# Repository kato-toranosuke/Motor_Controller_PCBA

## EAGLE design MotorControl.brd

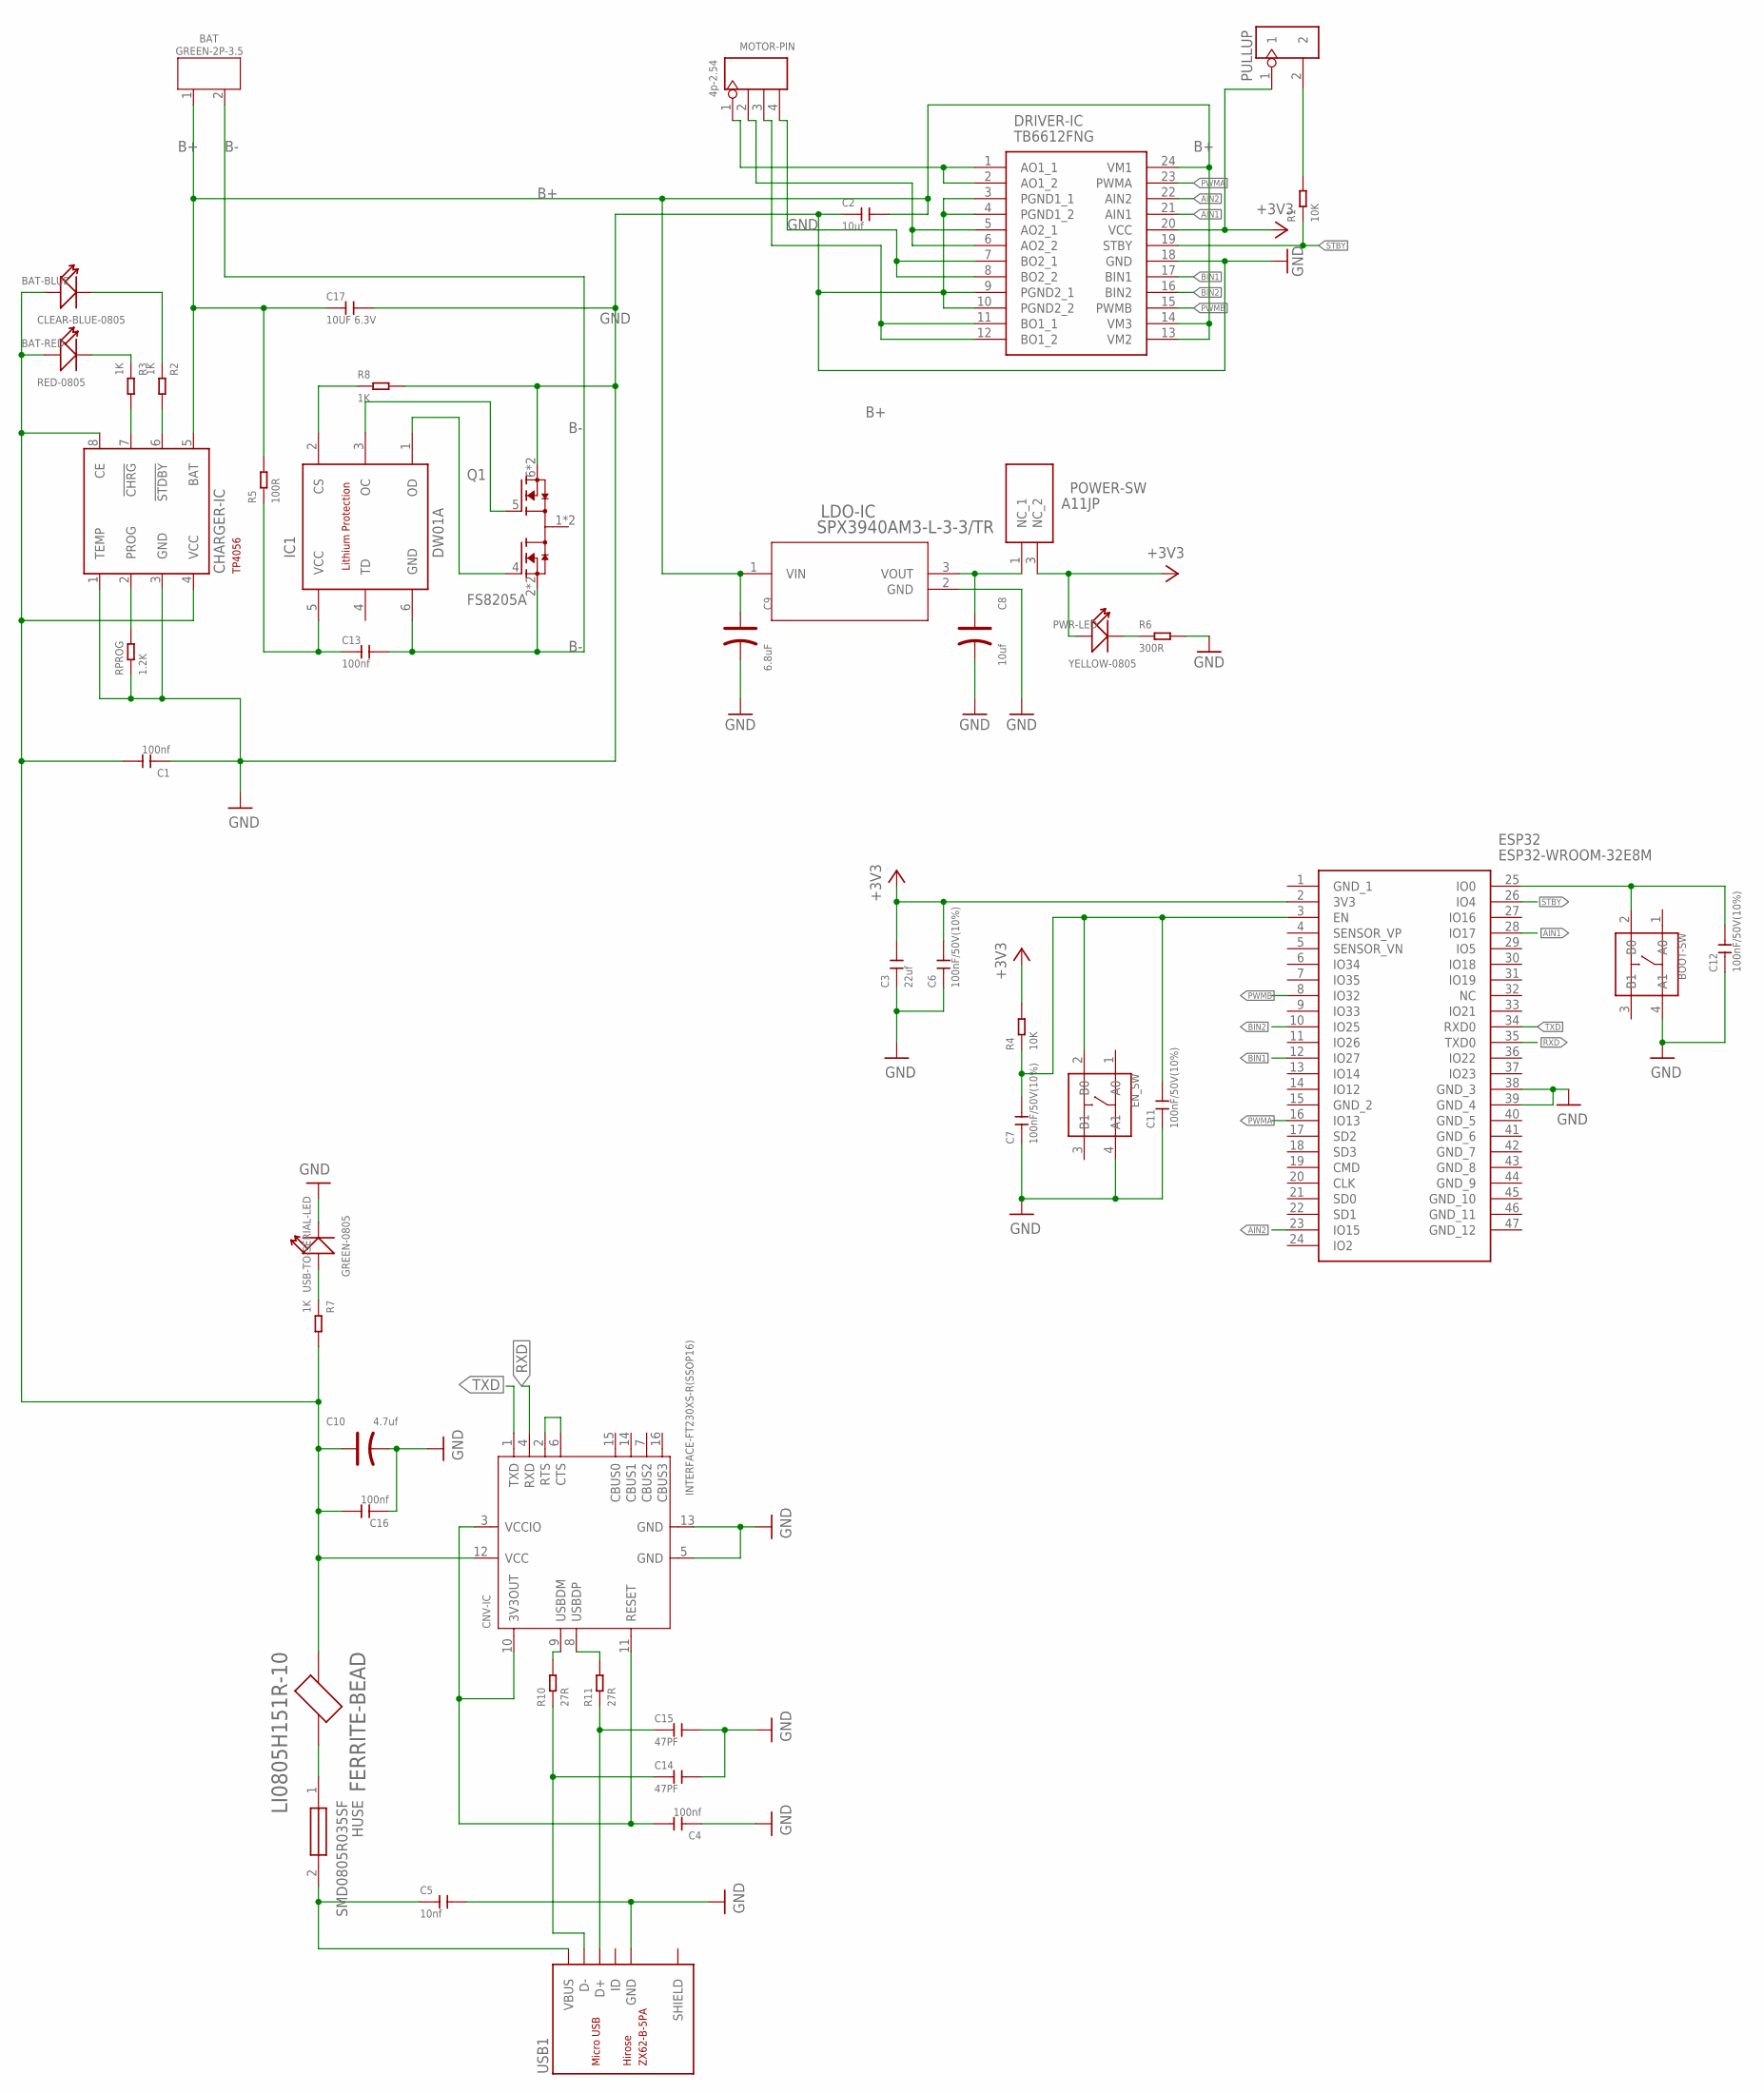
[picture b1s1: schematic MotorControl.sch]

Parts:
BAT: GREEN-2P-3.5; H2-3.5-7.0X7.0MM
BAT-BLUE: CLEAR-BLUE-0805; LED-0805
BAT-RED: RED-0805; LED-0805
BOOT-SW: SMD-SWITCH-TACTILE-SPST-NO(4P-D6.0MM); SW4-SMD-6.0X6.0X5.0MM
C1, C4, C13, C16: 100nf; C0805
C2: 10uf; C1206
C3: 22uf; C0805
C5: 10nf; C0805
C6, C7, C11, C12: 100nF/50V(10%); C0603
C8: 10uf; AVX-A
C9: 6.8uF; CAPPM3528X210N
C10: 4.7uf; AVX-A
C14, C15: 47PF; C0402
C17: 10UF 6.3V; C0603
CHARGER-IC: TP4056; SOT23-8; MPN TP4056
CNV-IC: INTERFACE-FT230XS-R(SSOP16); SSOP16-0.635-5X4MM
DRIVER-IC: TB6612FNG; SOP65P760X160-24N
EN_SW: SMD-SWITCH-TACTILE-SPST-NO(4P-D6.0MM); SW4-SMD-6.0X6.0X5.0MM
ESP32: ESP32-WROOM-32E8M; ESP32WROOM32E8MB
FERRITE-BEAD: LI0805H151R-10; FB_LI0805H151R-10
HUSE: SMD0805R035SF; MPN SMD0805R035SF
IC1: DW01A; SOT23-6
LDO-IC: SPX3940AM3-L-3-3/TR; SOT-223-3_VAR-AA
MOTOR-PIN: 4p-2.54; H4-2.54
POWER-SW: A11JP
PULLUP: DIP-BLACK-JUMPER; H2-2.54
PWR-LED: YELLOW-0805; LED-0805
Q1: FS8205A; SOP65P640X120-8N
R1, R4: 10K; R0603
R2, R3, R7: 1K; R0603
R5: 100R; R1206
R6: 300R; R0603
R8: 1K; R0805
R10, R11: 27R; R0805
RPROG: 1.2K; R0805
USB1: ZX62-B-5PA; MICRO-USB5+6P-SMD-0.65-AB
USB-TO-SERIAL-LED: GREEN-0805; LED-0805

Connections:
+3V3: C3.2, C6.2, DRIVER-IC.20 (VCC), ESP32.2 (3V3), POWER-SW.3 (NC_2), PULLUP.1, PWR-LED.+, R4.2
AIN1: DRIVER-IC.21 (AIN1), ESP32.28 (IO17)
AIN2: DRIVER-IC.22 (AIN2), ESP32.23 (IO15)
AO1: DRIVER-IC.1 (AO1_1), DRIVER-IC.2 (AO1_2), MOTOR-PIN.1
AO2: DRIVER-IC.5 (AO2_1), DRIVER-IC.6 (AO2_2), MOTOR-PIN.2
B+: BAT.1, C2.2, C9.1 (+), C17.1, CHARGER-IC.5 (BAT), DRIVER-IC.13 (VM2), DRIVER-IC.14 (VM3), DRIVER-IC.24 (VM1), LDO-IC.1 (VIN), R5.2
B-: BAT.2, C13.2, IC1.6 (GND), Q1.2 (S1), Q1.3 (S1)
BIN1: DRIVER-IC.17 (BIN1), ESP32.12 (IO27)
BIN2: DRIVER-IC.16 (BIN2), ESP32.10 (IO25)
BO1: DRIVER-IC.11 (BO1_1), DRIVER-IC.12 (BO1_2), MOTOR-PIN.3
BO2: DRIVER-IC.7 (BO2_1), DRIVER-IC.8 (BO2_2), MOTOR-PIN.4
GND: BOOT-SW.4 (A1), C1.1, C2.1, C3.1, C4.1, C5.2, C6.1, C7.1, C8.-, C9.2 (-), C10.-, C11.1, C12.1, C14.2, C15.2, C16.1, C17.2, CHARGER-IC.1 (TEMP), CHARGER-IC.3 (GND), CNV-IC.5 (GND), CNV-IC.13 (GND), DRIVER-IC.3 (PGND1_1), DRIVER-IC.4 (PGND1_2), DRIVER-IC.9 (PGND2_1), DRIVER-IC.10 (PGND2_2), DRIVER-IC.18 (GND), EN_SW.4 (A1), ESP32.38 (GND_3), ESP32.39 (GND_4), LDO-IC.2 (GND), Q1.6 (S2), Q1.7 (S2), R6.2, R8.2, RPROG.1, USB1.5 (GND), USB-TO-SERIAL-LED.-
unnamed: IC1.3 (OC), Q1.5 (G2)
unnamed: BAT-RED.-, R3.1
unnamed: R7.1, USB-TO-SERIAL-LED.+
unnamed: FERRITE-BEAD.2, HUSE.1
unnamed: C4.2, CNV-IC.3 (VCCIO), CNV-IC.10 (3V3OUT), CNV-IC.11 (RESET)
unnamed: CNV-IC.2 (RTS), CNV-IC.6 (CTS)
unnamed: CNV-IC.9 (USBDM), R10.2
unnamed: CNV-IC.8 (USBDP), R11.2
unnamed: C14.1, R10.1, USB1.2 (D-)
unnamed: IC1.1 (OD), Q1.4 (G1)
unnamed: CHARGER-IC.7 (!CHRG), R3.2
unnamed: CHARGER-IC.6 (!STDBY), R2.2
unnamed: BAT-BLUE.-, R2.1
unnamed: PWR-LED.-, R6.1
unnamed: C15.1, R11.1, USB1.3 (D+)
unnamed: CHARGER-IC.2 (PROG), RPROG.2
unnamed: C13.1, IC1.5 (VCC), R5.1
unnamed: IC1.2 (CS), R8.1
unnamed: PULLUP.2, R1.2
unnamed: C7.2, C11.2, EN_SW.2 (B0), ESP32.3 (EN), R4.1
unnamed: BOOT-SW.2 (B0), C12.2, ESP32.25 (IO0)
POWER_SW: C8.+, LDO-IC.3 (VOUT), POWER-SW.1 (NC_1)
PWMA: DRIVER-IC.23 (PWMA), ESP32.16 (IO13)
PWMB: DRIVER-IC.15 (PWMB), ESP32.8 (IO32)
RXD: CNV-IC.4 (RXD), ESP32.35 (TXD0)
STBY: DRIVER-IC.19 (STBY), ESP32.26 (IO4), R1.1
TXD: CNV-IC.1 (TXD), ESP32.34 (RXD0)
VBUS: C5.1, HUSE.2, USB1.1 (VBUS)
VIN+: BAT-BLUE.+, BAT-RED.+, C1.2, C10.+, C16.2, CHARGER-IC.4 (VCC), CHARGER-IC.8 (CE), CNV-IC.12 (VCC), FERRITE-BEAD.1, R7.2

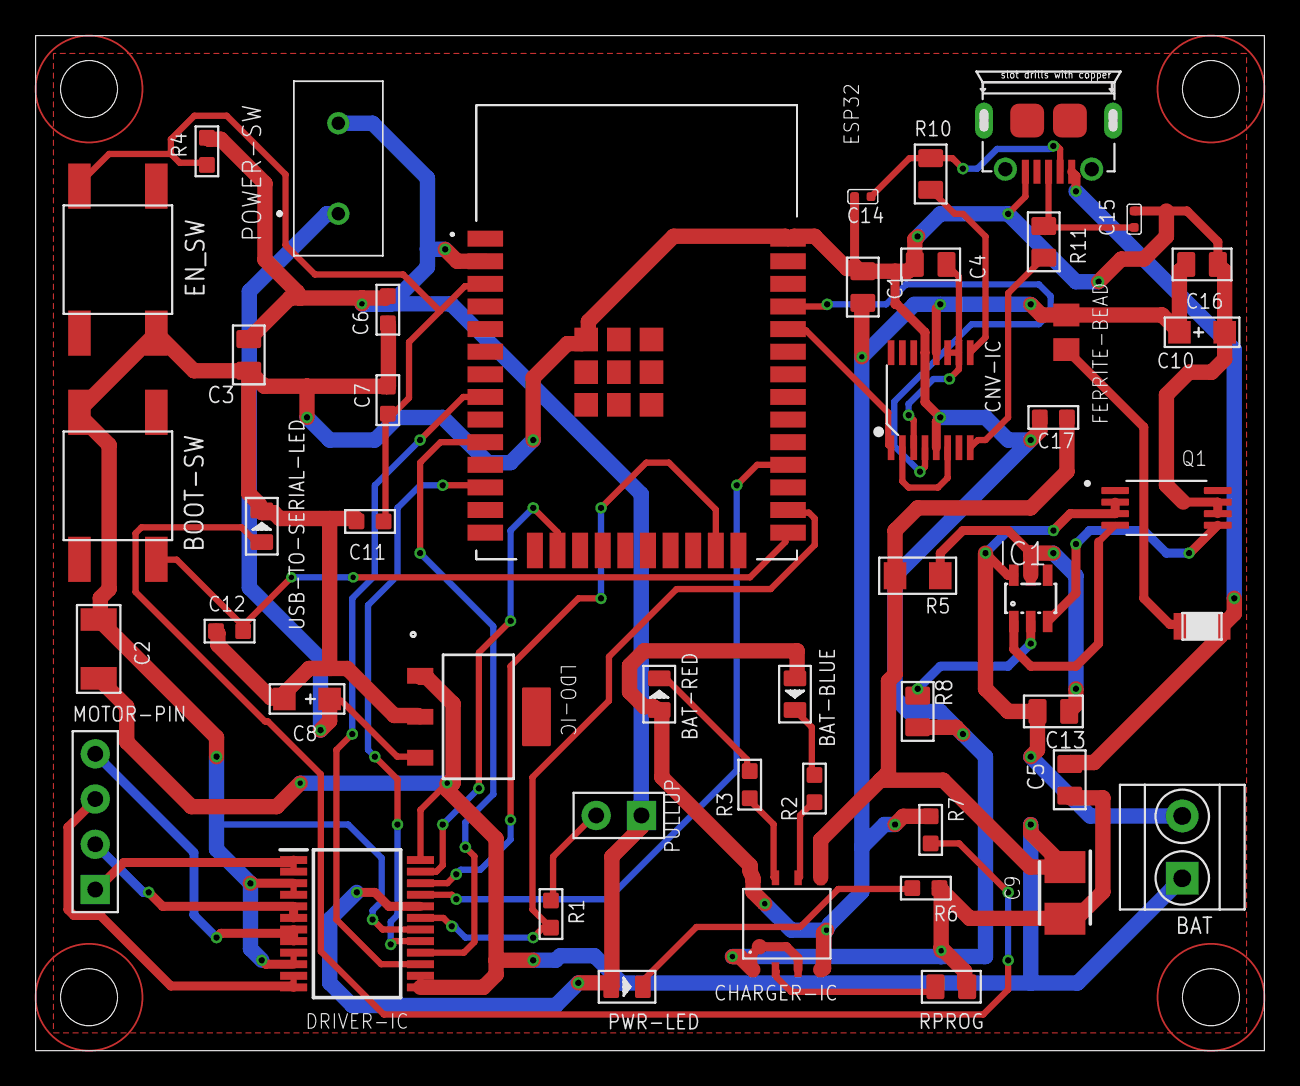
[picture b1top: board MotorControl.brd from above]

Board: 2 copper layers, 68.5 x 56.5 mm, 48 parts (0 on the bottom side), 41 nets.

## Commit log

2021-09-17 [Add] ボード図配線済み（ベタ塗り前）
2021-09-17 [Fix] ボード図においてGNDをbottomに配線
2021-09-17 [fix] ベタ塗り
2021-09-17 [fix] シルク作成
2021-09-20 [Fix] 20210920MT時点（４層）
2021-10-08 [Modify] 部品置換前。在庫チェック中
2021-10-08 [Add] add archive
2021-10-11 [M] ２面に対応
2021-10-11 [A] add output data
2021-10-14 [M] BOMにLinkを追加。発注可能な状態。

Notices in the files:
parts and their libraries:
COPYRIGHT: Copyright (C) 2018 Accelerated Designs. All rights reserved
